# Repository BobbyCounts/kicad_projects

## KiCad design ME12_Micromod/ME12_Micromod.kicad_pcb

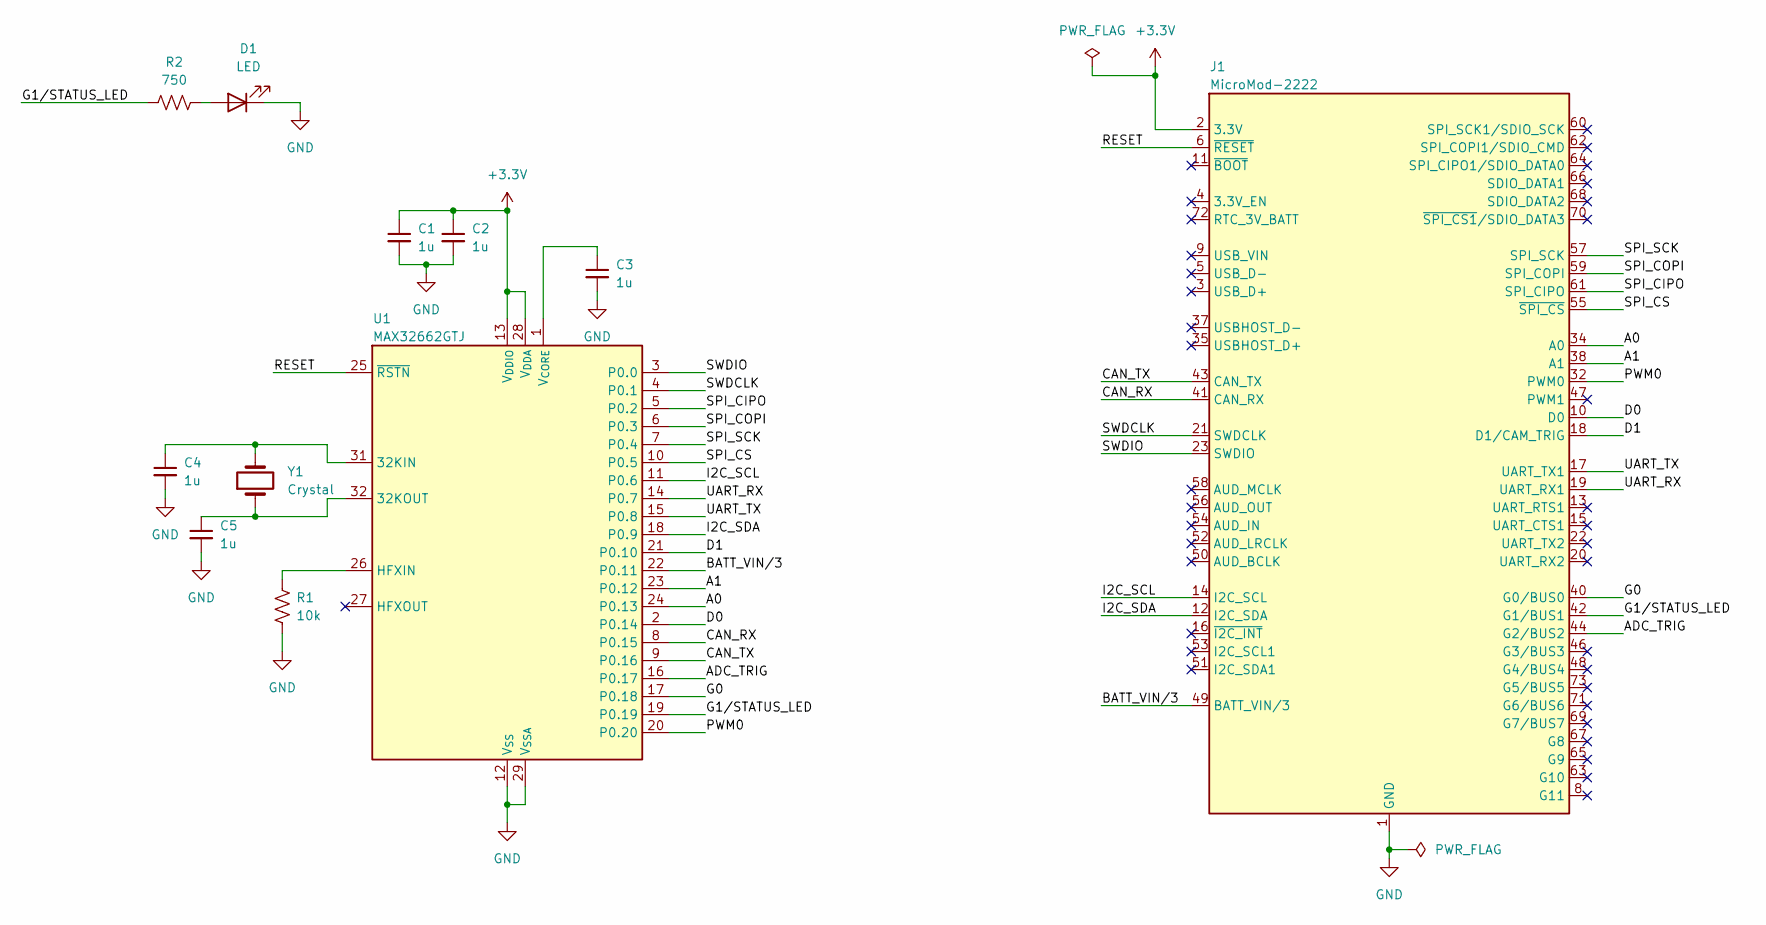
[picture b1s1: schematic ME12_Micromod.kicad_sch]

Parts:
C1, C2, C3, C4, C5: 1u; C_0603_1608Metric
D1: LED; LED_0603_1608Metric
J1: MicroMod-2222; micromod_processor
R1: 10k; R_0603_1608Metric
R2: 750; R_0603_1608Metric
U1: MAX32662GTJ; TQFN-32-1EP_5x5mm_P0.5mm_EP2.1x2.1mm
Y1: Crystal; ECX-16R

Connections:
+3.3V: C1.1, C2.1, J1.2 (3.3V), J1.74 (3.3V), U1.13 (V_{DDIO}), U1.28 (V_{DDA})
/A0: J1.34 (A0), U1.24 (P0.13)
/A1: J1.38 (A1), U1.23 (P0.12)
/ADC_TRIG: J1.44 (G2/BUS2), U1.16 (P0.17)
/BATT_VIN/3: J1.49 (BATT_VIN/3), U1.22 (P0.11)
/CAN_RX: J1.41 (CAN_RX), U1.8 (P0.15)
/CAN_TX: J1.43 (CAN_TX), U1.9 (P0.16)
/D0: J1.10 (D0), U1.2 (P0.14)
/D1: J1.18 (D1/CAM_TRIG), U1.21 (P0.10)
/G0: J1.40 (G0/BUS0), U1.17 (P0.18)
/G1/STATUS_LED: J1.42 (G1/BUS1), R2.1, U1.19 (P0.19)
/I2C_SCL: J1.14 (I2C_SCL), U1.11 (P0.6)
/I2C_SDA: J1.12 (I2C_SDA), U1.18 (P0.9)
/PWM0: J1.32 (PWM0), U1.20 (P0.20)
/RESET: J1.6 (~RESET), U1.25 (~RSTN)
/SPI_CIPO: J1.61 (SPI_CIPO), U1.5 (P0.2)
/SPI_COPI: J1.59 (SPI_COPI), U1.6 (P0.3)
/SPI_CS: J1.55 (~SPI_CS), U1.10 (P0.5)
/SPI_SCK: J1.57 (SPI_SCK), U1.7 (P0.4)
/SWDCLK: J1.21 (SWDCLK), U1.4 (P0.1)
/SWDIO: J1.23 (SWDIO), U1.3 (P0.0)
/UART_RX: J1.19 (UART_RX1), U1.14 (P0.7)
/UART_TX: J1.17 (UART_TX1), U1.15 (P0.8)
GND: C1.2, C2.2, C3.2, C4.2, C5.2, D1.1 (K), J1.1 (GND), J1.7 (GND), J1.33 (GND), J1.36 (GND), J1.39 (GND), J1.45 (GND), J1.75 (GND), J1.76 (GND), R1.2, U1.12 (V_{SS}), U1.29 (V_{SSA}), U1.30 (V_{SS}), U1.33 (V_{SS})
unnamed: D1.2 (A), R2.2
unnamed: C4.1, U1.31 (32KIN), Y1.2
unnamed: C5.1, U1.32 (32KOUT), Y1.1
unnamed: R1.1, U1.26 (HFXIN)
unnamed: C3.1, U1.1 (V_{CORE})

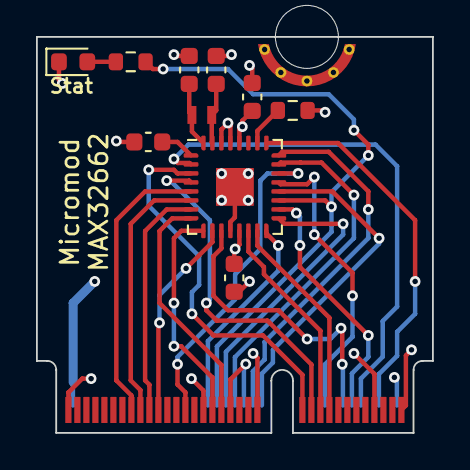
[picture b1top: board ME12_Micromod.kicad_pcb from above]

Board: 4 copper layers, 22.0 x 22.0 mm, 11 parts (0 on the bottom side), 29 nets.

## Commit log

2023-07-03 Add gitignore
2023-07-20 Add ME12 Micromod
